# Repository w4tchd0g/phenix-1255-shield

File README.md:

# phenix-1255-shield

Expansion board (shield) for the NXP **FRDM-MCXN947** development board, built around the Semtech **SX1255** RF transceiver (TX 440 MHz, RX 430 MHz).

Together with the firmware it turns the FRDM board into a multimode SDR transceiver for base stations: TETRA today, DMR, FM and more modes planned. The I/Q samples are streamed to a host over HS USB or Ethernet.

This board is the hardware part of [phenix-1255-sw](https://github.com/w4tchd0g/phenix-1255-sw). It is a modified version of [Phenix-1255-HW](https://github.com/labdvm/Phenix-1255-HW) by Z32IT ([@labdvm](https://github.com/labdvm)), see [Changes from Phenix-1255-HW](#changes-from-phenix-1255-hw).

> **Status:** design complete and ready for fabrication. The schematic passes ERC without errors, the PCB passes DRC without errors and without unrouted connections. The Gerber files for JLCPCB and PCBWay are in [`production/`](#fabrication). Before the first power-up, read the [bring-up checklist](#bring-up-checklist).

## Preview

| Top | Bottom |
|---|---|
|  |  |

### SMA connector options

J5 (TX) and J6 (RX) use a hybrid land pattern that takes either connector type. Populate only one connector per port.

| Vertical SMD jack (CONSMA001-SMD-G) | Edge mount (Samtec SMA-J-P-H-ST-EM1) |
|---|---|
|  |  |

- **CONSMA001-SMD-G:** reflowed with the other parts. The unused edge-mount centre pad forms a short open stub (about 1 pF). At 430/440 MHz it has practically no effect (return loss at the port ≥ 34 dB).
- **Edge mount:** the edge-mount pads have no paste, so solder the jack by hand after reflow. The GND pads connect to the fill through thermal reliefs to make this easier. Use a large chisel tip and preheat the board from below (about 120–150 °C).

## Changes from Phenix-1255-HW

The basic hardware concept comes from [labdvm/Phenix-1255-HW](https://github.com/labdvm/Phenix-1255-HW) (Copyright © Z32IT 2026, CERN-OHL-P-2.0). This project changes revision V2 of it as follows (2026-11):

**RF**

- **Antenna matching:** new matching networks. TX: an L-network transforms the 50 Ω of the LFCN-490+ to the 100 Ω optimum load of RFO_P (before: 100 pF straight to the filter). RX: 100 pF / 33 nH / 68 nH for the 200 Ω LNA input (before: 39 nH series, 82 nH shunt). See [RF matching networks](#rf-matching-networks).
- **RF connectors:** SMA instead of U.FL, with a hybrid land pattern for J5/J6 that takes either a vertical SMD jack or an edge-mount jack, see [SMA connector options](#sma-connector-options).
- **Port protection:** each SMA port has a 100 nH DC shunt and a low-capacitance TVS diode (before: 1 MΩ to GND). A BAV99 limiter protects the RX input of the SX1255.
- **PCB:** 4 layers instead of 2, with 50 Ω coplanar waveguides on a solid GND plane, via fences along the RF lines and a GND stitching grid, see [PCB](#pcb). No mounting holes.
- **Reference clock:** 2520 footprint only, TCXO AC-coupled to XTB through 10 nF (before: direct connection with 10 kΩ / 10 pF to GND).

**Power**

- **3.3 V regulator:** an ST LDK130M33R (SOT-23-5) replaces the Microchip MCP1703A (SOT-223). It runs directly from `+5v0`; the PTC fuse, the TVS array and the ferrite bead at the input are gone.
- **Supply split:** the LDO only supplies the RF part (SX1255, TCXO, PA load switch). Display, buttons and jumpers run from the FRDM 3.3 V rail. The 1 Ω series resistors in the SX1255 supply pins are gone. See [Power](#power).
- **PA supply switching:** an integrated load switch (TPS22917) replaces the P-channel MOSFET. The *bypass* solder jumper is gone.

**Digital interface and MCU pins**

- **`~PA_EN` pin:** moved from P2_4 to P1_23 (J9.23) for better routing.
- **Series resistors:** 33 Ω at the driving end of each SX1255 signal. NSS has a 10 kΩ pull-up, CK_IN and Q_IN are bridged and pulled down with one 10 kΩ resistor, `SX_RST` has no series resistor.
- **Hardware ID:** three solder jumpers (JP1–JP3, `HW_ID_0`…`HW_ID_2`) encode the board version, so that the firmware can support several hardware versions (up to 8). This board is **hardware ID 0** (all jumpers open).
- **Buttons:** Panasonic EVQ-Q2 instead of C&K PTS647. *OK* and *→* swapped pins: *OK* is now on P1_22 (J3.3), *→* on P4_12 (J4.1).
- **Status LEDs:** five instead of four; the new PA LED lights while the PA is powered. The LEDs on the GPIOs were reassigned: P0_14 green *OK* (before: red *Err*), P0_22 yellow *INFO* (before: *Warn*), P0_15 red *ERR* (before: green *Good*). 1 kΩ instead of 1.5 kΩ series resistors.
- **Display:** footprint with the module outline (DS1) instead of a 1×4 socket, without series resistors in SCL/SDA.

See [MCU pin assignment](#mcu-pin-assignment) for the pins. The TX driver amplifier of the *V2 Plus* variant is not part of this design.

## Overview

| | |
|---|---|
| Base board | [NXP FRDM-MCXN947](https://www.nxp.com/design/design-center/development-boards-and-designs/FRDM-MCXN947) |
| EDA tool | KiCad 10 |
| Board size | 118 × 55 mm, R2 corners, 17 × 5 mm cutout (R1 corners) on the left edge for the Ethernet jack of the FRDM board |
| Stackup | 4 layers, 1.6 mm, JLCPCB JLC04161H-7628 |
| Assembly | all parts on the top side |
| Based on | [Phenix-1255-HW](https://github.com/labdvm/Phenix-1255-HW) by Z32IT (CERN-OHL-P-2.0), see [Changes from Phenix-1255-HW](#changes-from-phenix-1255-hw) |
| Shield template | FRDM-MCXN947 shield template from [wavenumber-eng/frdm-templates](https://github.com/wavenumber-eng/frdm-templates) (CC0): board outline, header placement and root schematic |

## Components

| Function | Part | Manufacturer |
|---|---|---|
| RF transceiver | SX1255IWLTRT (QFN-32, 5 × 5 mm) | Semtech |
| Reference clock | TG2520SMN 38.4 MHz TCXO (2.5 × 2.0 mm) | Epson |
| SAW filter 430 MHz (RX) | TA0655A | Tai-Saw |
| Low-pass filter (TX) | LFCN-490+ | Mini-Circuits |
| RF connectors (TX, RX) | CONSMA001-SMD-G (vertical, SMD) or SMA-J-P-H-ST-EM1 (edge mount), see [SMA connector options](#sma-connector-options) | TE / Linx, Samtec |
| ESD protection RF ports | PESD5V0F1BL | Nexperia |
| RX input limiter | BAV99 | Nexperia |
| LDO 3.3 V | LDK130M33R | ST |
| PA supply load switch | TPS22917LDBVR (active-low enable) | TI |
| Display | OLED 0.96″ 128×64, SSD1306, I²C, pin order GND/VDD/SCL/SDA (module with on-board pull-ups) | – |
| Tactile switch (SPST-NO, 6.5 × 6 mm, SMD), 3× | EVQ-Q2Y03W | Panasonic |
| Status LEDs 0603, 5× (PWR, PA, OK, INFO, ERR) | 150060xS75000 (green, yellow, red) | Würth |
| Hardware ID, 3× | solder jumper, open (hardware ID 0) | – |
| Headers to the FRDM board | Samtec SSQ (from the template) | Samtec |

Passives are 0603 (resistors UNI-ROYAL `0603WAF…`, capacitors Samsung/Murata/Yageo, RF inductors Murata `LQW18AN…`). The manufacturer part numbers are stored in the `MPN` field of the symbols.

## Circuit

### Power

| Net | Source | Loads |
|---|---|---|
| `+5v0` | FRDM header J3.10 | LDO input |
| `+3.3V_LDO` | LDO on the shield (enable tied to `+5v0`) | SX1255 VBAT1/VBAT2, TCXO, load switch input, PWR LED |
| `VBAT3` | load switch, controlled by `~PA_EN` | SX1255 VBAT3 (PA supply), PA LED |
| `+3v3` | FRDM header (J3.4, J3.8, J9.21, J8.1) | display, buttons, HW-ID jumpers, `~PA_EN` pull-up |

The RF part runs from its own low-noise LDO. Only the MCU-side parts use the FRDM 3.3 V rail.

`~PA_EN` is **active low** and pulled up to `+3v3` with 100 kΩ, so the PA supply stays off until the firmware drives the pin low. The load switch uses quick output discharge (QOD tied to VOUT). CT is left open, which gives the fastest turn-on.

### RF

- **TX:** SX1255 RFO_P → matching network (100 pF / 3.6 pF / 18 nH) → LFCN-490+ low-pass → SMA **J5 (TX)**. RFO_N is AC-coupled to GND.
- **RX:** SMA **J6 (RX)** → TA0655A SAW filter → matching network (100 pF / 33 nH / 68 nH) → SX1255 RFI, with a BAV99 limiter at the RFI pin.
- **SMA ports:** each port has a 100 nH DC shunt to GND (L1/L5) and a low-capacitance TVS diode (D1/D8). Together with the stub of the SMD jack they need no further matching (return loss ≥ 24 dB).
- **RF lines:** 50 Ω coplanar waveguide with ground (CPWG) on F.Cu over the solid GND plane In1, 0.30 mm track, 0.30 mm gap (0.20 mm inside the SX1255 courtyard). A field-solver check gives about 52 Ω with solder mask, i.e. a return loss of about 33 dB. The lines are electrically short (longest RF net 23 mm ≈ 23° at 440 MHz).
- **Reference clock:** the 38.4 MHz TCXO drives XTB through 10 nF, XTA is left open (TCXO connection per the datasheet). 38.4 MHz is above the specified FXOSC range of the SX1255 (32 / 36 / 36.864 MHz min/typ/max, datasheet Rev. 3.0, table 5). It has been **tested and works**; keep in mind that it is outside the specification. All frequencies derived from FXOSC (PLL step, I/Q sample rate) scale with 38.4 MHz.

`scripts/rf_calc.py` reproduces all RF numbers in this README (CPWG impedance, SMA stub, port shunts, matching networks). It runs with the standard library; the field solver part also needs numpy and scipy (`pip install numpy scipy`).

### RF matching networks

The networks adapt the SX1255 impedances to the 50 Ω of the LFCN-490+ and the TA0655A. They are based on the SX1255 datasheet (Rev. 3.0) and on separate front-end design notes (*SX1255 RF front end: TX 440 MHz / RX 430 MHz*, not in this repository). The values are calculated with ideal components and are **start values**; the final tuning is done on the board with a VNA.

#### TX: 100 Ω → 50 Ω

```
RF_OP ──C14 100p──┬──L2 18n──► LFCN-490+ (50 Ω) ──► J5
                  │
               C13 3.6p
                  │
                 GND
RF_ON ──C15 100p── GND
```

The datasheet specifies an optimum load of **100 Ω differential** between RF_OP and RF_ON (section 3.4.4, peak output power +5 dBm). The output is used single-ended: C15 ties RF_ON to ground for RF, so RF_OP has to see 100 Ω. The low-pass L-network (Q = 1) transforms 50 Ω up to 100 Ω:

| Element | Calculated | Used |
|---|---|---|
| Shunt C | 3.62 pF | **C13 = 3.6 pF** (C0G, ±0.1 pF) |
| Series L | 18.09 nH | **L2 = 18 nH** (wirewound, ±2 %) |

C14 (100 pF) only blocks DC. With the values used, RF_OP sees 99.5 − j3.1 Ω at 440 MHz (return loss 35.9 dB, ≥ 22 dB from 400 to 480 MHz, ≥ 29.9 dB within the component tolerances). The network adds 3.3 dB attenuation at the 2nd and 9.5 dB at the 3rd harmonic on top of the LFCN-490+.

**Tuning element: C13.** The output capacitance of RF_OP is not specified and appears in parallel with C13. Trim C13 for maximum output power at J5.

#### RX: 50 Ω → 200 Ω

```
J6 ──► TA0655A (50 Ω) ──C21 100p──L4 33n──┬────────┬────────┬──► RF_IN (200 Ω)
                                          │        │        │
                                        L3 68n   D4 BAV99  C_pin (LNA input)
                                          │        │        │
                                         GND      GND      GND
```

RF_IN is a common-gate LNA with an input impedance of 50 Ω or 200 Ω, selected with the bit LnaZin in RegRxAnaGain (section 3.6.2). The network is designed for **200 Ω** (see [Firmware notes](#firmware-notes)).

The ideal L-network at 430 MHz is a series L of 32.05 nH (**L4 = 33 nH**) and a shunt C of 3.21 pF at RF_IN. There is no shunt capacitor on the board: that capacitance comes from the RF_IN node itself (LNA input, BAV99, pad, track). The design assumes it is larger than needed, and **L3 (68 nH)** compensates the excess (68 nH cancels 2.01 pF at 430 MHz). L3 also gives RF_IN a DC path to ground. The values used require a **total capacitance of 5.24 pF at RF_IN**. The datasheet does not specify it, so this is the critical assumption of the RX match:

| Total capacitance at RF_IN | Return loss at 430 MHz | Best match at |
|---|---|---|
| 4.0 pF | 10.0 dB | 495 MHz |
| 4.5 pF | 14.2 dB | 466 MHz |
| 5.0 pF | 23.7 dB | 441 MHz |
| **5.24 pF** | **40.0 dB** | **431 MHz** |
| 5.5 pF | 23.1 dB | 420 MHz |
| 6.0 pF | 14.0 dB | 401 MHz |

With the nominal value the return loss is ≥ 20 dB from 414 to 447 MHz, much wider than the 4 MHz passband of the TA0655A.

**Tuning element: L3.** For a match at 430 MHz: 4 pF → 177 nH, 5 pF → 77 nH, 6 pF → 49 nH, 7 pF → 36 nH. Procedure (from the design notes): before the TA0655A is fitted, solder a coax pigtail to its output pad (pin E) and measure S11 towards the SX1255. If the minimum is above 430 MHz, increase L3; if it is below, decrease L3. Adjust the depth with L4 (27 / 33 / 39 nH). Target S11 ≤ −10 dB, then optimise for best sensitivity.

### Digital interface

All signals between the SX1255 and the headers have 33 Ω series resistors at the driving end: next to the SX1255 for its outputs (`CK_OUT`, `I_OUT`, `MISO`, `DIO0..3`), next to the headers for the MCU outputs (`SCK`, `MOSI`, `NSS`, `I_IN`). NSS has a 10 kΩ pull-up to `+3.3V_LDO`. CK_IN and Q_IN are unused inputs: pins 11 and 12 are bridged next to the SX1255 and pulled down together with one 10 kΩ resistor (R4). Q_OUT and XTA are not connected.

## MCU pin assignment

| Net | Header | FRDM signal | Function |
|---|---|---|---|
| `SCK` | J2.12 | P0_25 / FC1_SCK | SX1255 SPI |
| `MISO` | J2.10 | P0_26 / FC1_SDI | SX1255 SPI |
| `MOSI` | J2.8 | P0_24 / FC1_SDO | SX1255 SPI |
| `NSS` | J1.16 | P0_31 | SX1255 SPI chip select (GPIO) |
| `SX_RST` | J1.6 | P0_29 | SX1255 reset (active high) |
| `DIO0` | J2.2 | P0_28 | SX1255 DIO0 |
| `DIO1` | J1.10 | P0_30 / P4_13 | SX1255 DIO1 |
| `DIO2/WS` | J1.13 | P3_19 / SAI1_RX_FS | SX1255 DIO2, I/Q word select |
| `DIO3` | J2.13 | P0_19 | SX1255 DIO3 |
| `CK_OUT` | J1.9 | P3_18 / SAI1_RX_BCLK | I/Q bit clock from SX1255 |
| `I_OUT` | J1.15 | P3_21 / SAI1_RXD0 | I/Q data SX1255 → MCU |
| `I_IN` | J1.5 | P3_20 / SAI1_TXD0 | I/Q data MCU → SX1255 |
| `~PA_EN` | J9.23 | P1_23 / EZH_LCD_RD | PA supply enable, active low |
| `SDA` | J2.17 | P1_0 | Display I²C |
| `SCL` | J2.15 | P1_1 | Display I²C |
| `BTN_0` | J3.1 | P2_0 | Button S1 (`<--`) |
| `BTN_1` | J3.3 | P1_22 | Button S2 (`OK`) |
| `BTN_2` | J4.1 | P4_12 / P0_21 | Button S3 (`-->`) |
| `LED_0` | J4.6 | P0_14 | LED OK (green) |
| `LED_1` | J4.8 | P0_22 | LED INFO (yellow) |
| `LED_2` | J4.10 | P0_15 (solder jumper SJ8 1-2, FRDM default) | LED ERR (red) |
| `HW_ID_0` | J9.5 | P1_19 / EZH_LCD_D15_CAMERA_RST | Hardware ID bit 0 |
| `HW_ID_1` | J9.12 | P3_4 | Hardware ID bit 1 |
| `HW_ID_2` | J9.11 | P3_5 | Hardware ID bit 2 |

Where the template lists two MCU pins (e.g. `P0_15 / P2_0`), the FRDM board routes the header pin to one of them via a solder jumper or resistor option. The pins above are the defaults from the FRDM-MCXN947 user manual (UM12018 Rev. 2.0). Some MCU pins also reach a second header on the FRDM board; on this shield the second pin is always left unconnected:

- P2_0 (`BTN_0`, J3.1) also goes to J9.25 (R167). It only reaches J4.10 if SJ8 is changed to 2-3, which would short `BTN_0` and `LED_2`. **Leave SJ8 on the FRDM board in its default position 1-2.**
- P1_22 (`BTN_1`, J3.3) also goes to J9.24.
- P1_23 (`~PA_EN`, J9.23) also goes to J1.8 (SJ1 1-2, default).

### Firmware notes

- **Buttons and HW-ID jumpers** switch to `+3v3` and have no external pull-downs. Enable the **internal pull-downs** on `BTN_x` and `HW_ID_x`. A pressed button or a closed jumper reads as `1`.
- **LEDs** `LED_0..2` are active high (1 kΩ to the LED). The PWR LED is always on, the PA LED lights while `VBAT3` is powered.
- **`SX_RST`** must stay **floating** in normal operation, as required by the SX1255 datasheet. Configure the GPIO as an input without pull resistor and drive it high only to reset.
- **`~PA_EN`**: drive it low to power the PA, drive it high or release it to switch the PA off.
- **LNA input impedance**: keep LnaZin (RegRxAnaGain, register 0x0C bit 0, reset value 1) at 1 = 200 Ω. The RX matching is designed for it; 50 Ω detunes the RX input.
- **I/Q interface**: SAI1 receives with the bit clock and frame sync from the SX1255; the transmitter has to run synchronously to the receiver.
- **Reference clock**: FXOSC is 38.4 MHz, not the 36 MHz of the datasheet examples. Calculate PLL and sample-rate settings with 38.4 MHz.

## PCB

### Stackup

JLCPCB JLC04161H-7628, 1.6 mm, 4 layers:

| Layer | Use | Dielectric to next layer |
|---|---|---|
| F.Cu | signals and RF (CPWG), GND fill | 0.21 mm prepreg 7628, εr 4.4 |
| In1.Cu | solid GND plane, no routing | 1.065 mm core, εr 4.6 |
| In2.Cu | power plane (`+3v3`, `+3.3V_LDO` and `+5v0` areas), GND below the RF section | 0.21 mm prepreg 7628, εr 4.4 |
| B.Cu | signals (SPI, DIO, SDA), GND fill | – |

The RF section has no vias in the signal path and no tracks on the inner layers or B.Cu. The GND layers are tied together with via fences along the RF lines and a stitching grid; the SX1255 exposed pad has thermal vias. Design minimums: 0.15 mm track and clearance, 0.3 mm drill, 0.5 mm via diameter (vias used: 0.6 / 0.3 mm and 0.8 / 0.4 mm).

## Fabrication

Production files are in `production/`:

- `production/phenix-1255-shield-gerber.zip` – upload this to JLCPCB or PCBWay (Gerber X1, Protel extensions, Excellon drill, PTH and NPTH separate).
- `production/gerber/` – the same files unpacked, plus the drill maps.

Order settings:

- **JLCPCB:** 4 layers, 1.6 mm, stackup **JLC04161H-7628** (the RF lines are calculated for it), 1 oz outer copper.
- **PCBWay:** 4 layers, 1.6 mm, 1 oz outer copper. The standard stackup is not guaranteed to match, so specify the [stackup](#stackup) in the order remark: layer order F.Cu (`.gtl`), In1.Cu (`.g1`), In2.Cu (`.g2`), B.Cu (`.gbl`); 0.21 mm prepreg 7628 between F.Cu and In1.Cu. The 50 Ω CPWG on F.Cu (0.30 mm track, 0.30 mm gap to the coplanar GND, reference In1.Cu) depends on that prepreg thickness.

Regenerate the files after every layout change:

```sh
./scripts/gerber.sh   # aborts if the DRC reports errors or unconnected items
./scripts/render.sh   # updates the images in docs/img/
```

### Assembly notes

- All SMD parts are on the top side. Populate **one** SMA connector type per port (see [SMA connector options](#sma-connector-options)).
- The FRDM headers J1–J4, J8 and J9 are marked *Do not populate* on the PCB, so they are not in a BOM or position file exported from the PCB. Solder them by hand.
- This board is **hardware ID 0**: leave the jumpers JP1–JP3 open. Do not bridge them, otherwise the firmware detects a different hardware version.
- If the RX match is to be measured (see [RF matching networks](#rf-matching-networks)), leave the TA0655A off the first board.

## Bring-up checklist

These points cannot be checked on paper and need a measurement on the first board:

- **TX output:** check the single-ended output on RFO_P (no DC feed) against the Semtech reference design, and trim C13 for maximum output power.
- **RX match:** the match assumes 5.24 pF at RF_IN, which the datasheet does not specify. Measure S11 at the TA0655A output and adjust L3/L4.
- **PA supply:** confirm that the SX1255 tolerates VBAT3 switched off while VBAT1/VBAT2 are powered.
- **Reference clock:** 38.4 MHz is outside the SX1255 specification (tested and working, see [RF](#rf)).

## Project structure

```
phenix-1255-shield/
├── phenix-1255-shield.kicad_pro    # project file – open this one
├── phenix-1255-shield.kicad_sch    # root schematic: FRDM headers, PWR_FLAGs
├── schematic.kicad_sch             # sub-sheet: SX1255, RF, power, UI
├── phenix-1255-shield.kicad_pcb    # PCB
├── phenix-1255-shield.kicad_dru    # custom design rules (RF, stitching)
├── phenix-1255-shield.kicad_sym    # symbols from the template
├── sym-lib-table / fp-lib-table    # project libraries
├── empty.kicad_wks                 # drawing sheet
├── scripts/gerber.sh               # Gerber and drill files for JLCPCB and PCBWay
├── scripts/render.sh               # renders the images in docs/img/
├── scripts/sma_variant.py          # helper for render.sh: SMD / edge-mount SMA view
├── scripts/trim.py                 # helper for render.sh: crops the images to the board
├── scripts/rf_calc.py              # CPWG impedance, SMA stub and matching network calculation
├── scripts/make_3d_models.py       # generates the simplified 3D models in ext_parts/3d/
├── docs/img/                       # rendered PCB images
├── production/                     # Gerber and drill files (generated)
├── ext_parts/                      # project-specific symbols, footprints and 3D models
└── LICENSE                         # CERN-OHL-P-2.0
```

## Usage

1. Clone the repository.
2. Open `phenix-1255-shield.kicad_pro` in KiCad 10.

The project-specific libraries are linked relative to the project via `${KIPRJMOD}`. Standard parts and their 3D models come from the KiCad 10 libraries that are installed with KiCad. Nothing else needs to be installed or configured.

**Notes:**

- According to NXP, the connectors in the template are 2–6 mil off from the exact Arduino positions. This is a design bug of the FRDM-MCXN947 itself; the shield still mates with the board.
- Always double-check the header IO assignments against the current FRDM-MCXN947 documentation before ordering boards.

## License

This project (schematics, PCB, the libraries in `ext_parts/`, scripts and documentation) is a modified version of [Phenix-1255-HW](https://github.com/labdvm/Phenix-1255-HW), Copyright © Z32IT 2026 (see [Changes from Phenix-1255-HW](#changes-from-phenix-1255-hw)), and is licensed under the [CERN Open Hardware Licence Version 2 – Permissive](LICENSE) (CERN-OHL-P-2.0), except for the third-party content listed below.

Third-party content:

- **Shield template** ([wavenumber-eng/frdm-templates](https://github.com/wavenumber-eng/frdm-templates), FRDM-MCXN947 KiCad template): board outline, header footprints and their placement, root schematic with the header symbols (`phenix-1255-shield.kicad_sch`, `phenix-1255-shield.kicad_sym`). [CC0 1.0](https://creativecommons.org/publicdomain/zero/1.0/)
- **Display footprint** `Display_128x64_096_I2C`: by TG9541 ([kicad-footprints](https://github.com/TG9541/kicad-footprints)), [CC0 1.0](https://creativecommons.org/publicdomain/zero/1.0/)
- **SMA edge-mount option:** the edge-mount pads in `CONSMA001-SMD-G_EdgeHybrid` and the 3D model `SMA_Samtec_SMA-J-P-H-ST-EM1_EdgeMount.step` are derived from the [KiCad libraries](https://www.kicad.org/libraries/license/) (footprint and 3D model `SMA_Samtec_SMA-J-P-H-ST-EM1_EdgeMount`), [CC-BY-SA 4.0](https://creativecommons.org/licenses/by-sa/4.0/). The changes (merged land pattern, added insulator and centre socket) are under the same license.
- **Standard parts:** footprints and 3D models from the KiCad libraries are referenced, not included (CC-BY-SA 4.0 with the KiCad library exception for designs).

Datasheets are not part of this repository; the `Datasheet` field of each part links to the manufacturer.

This source is distributed **WITHOUT ANY EXPRESS OR IMPLIED WARRANTY, INCLUDING OF MERCHANTABILITY, SATISFACTORY QUALITY AND FITNESS FOR A PARTICULAR PURPOSE**. Please see the CERN-OHL-P-2.0 for applicable conditions.

Source location: <https://github.com/w4tchd0g/phenix-1255-shield>

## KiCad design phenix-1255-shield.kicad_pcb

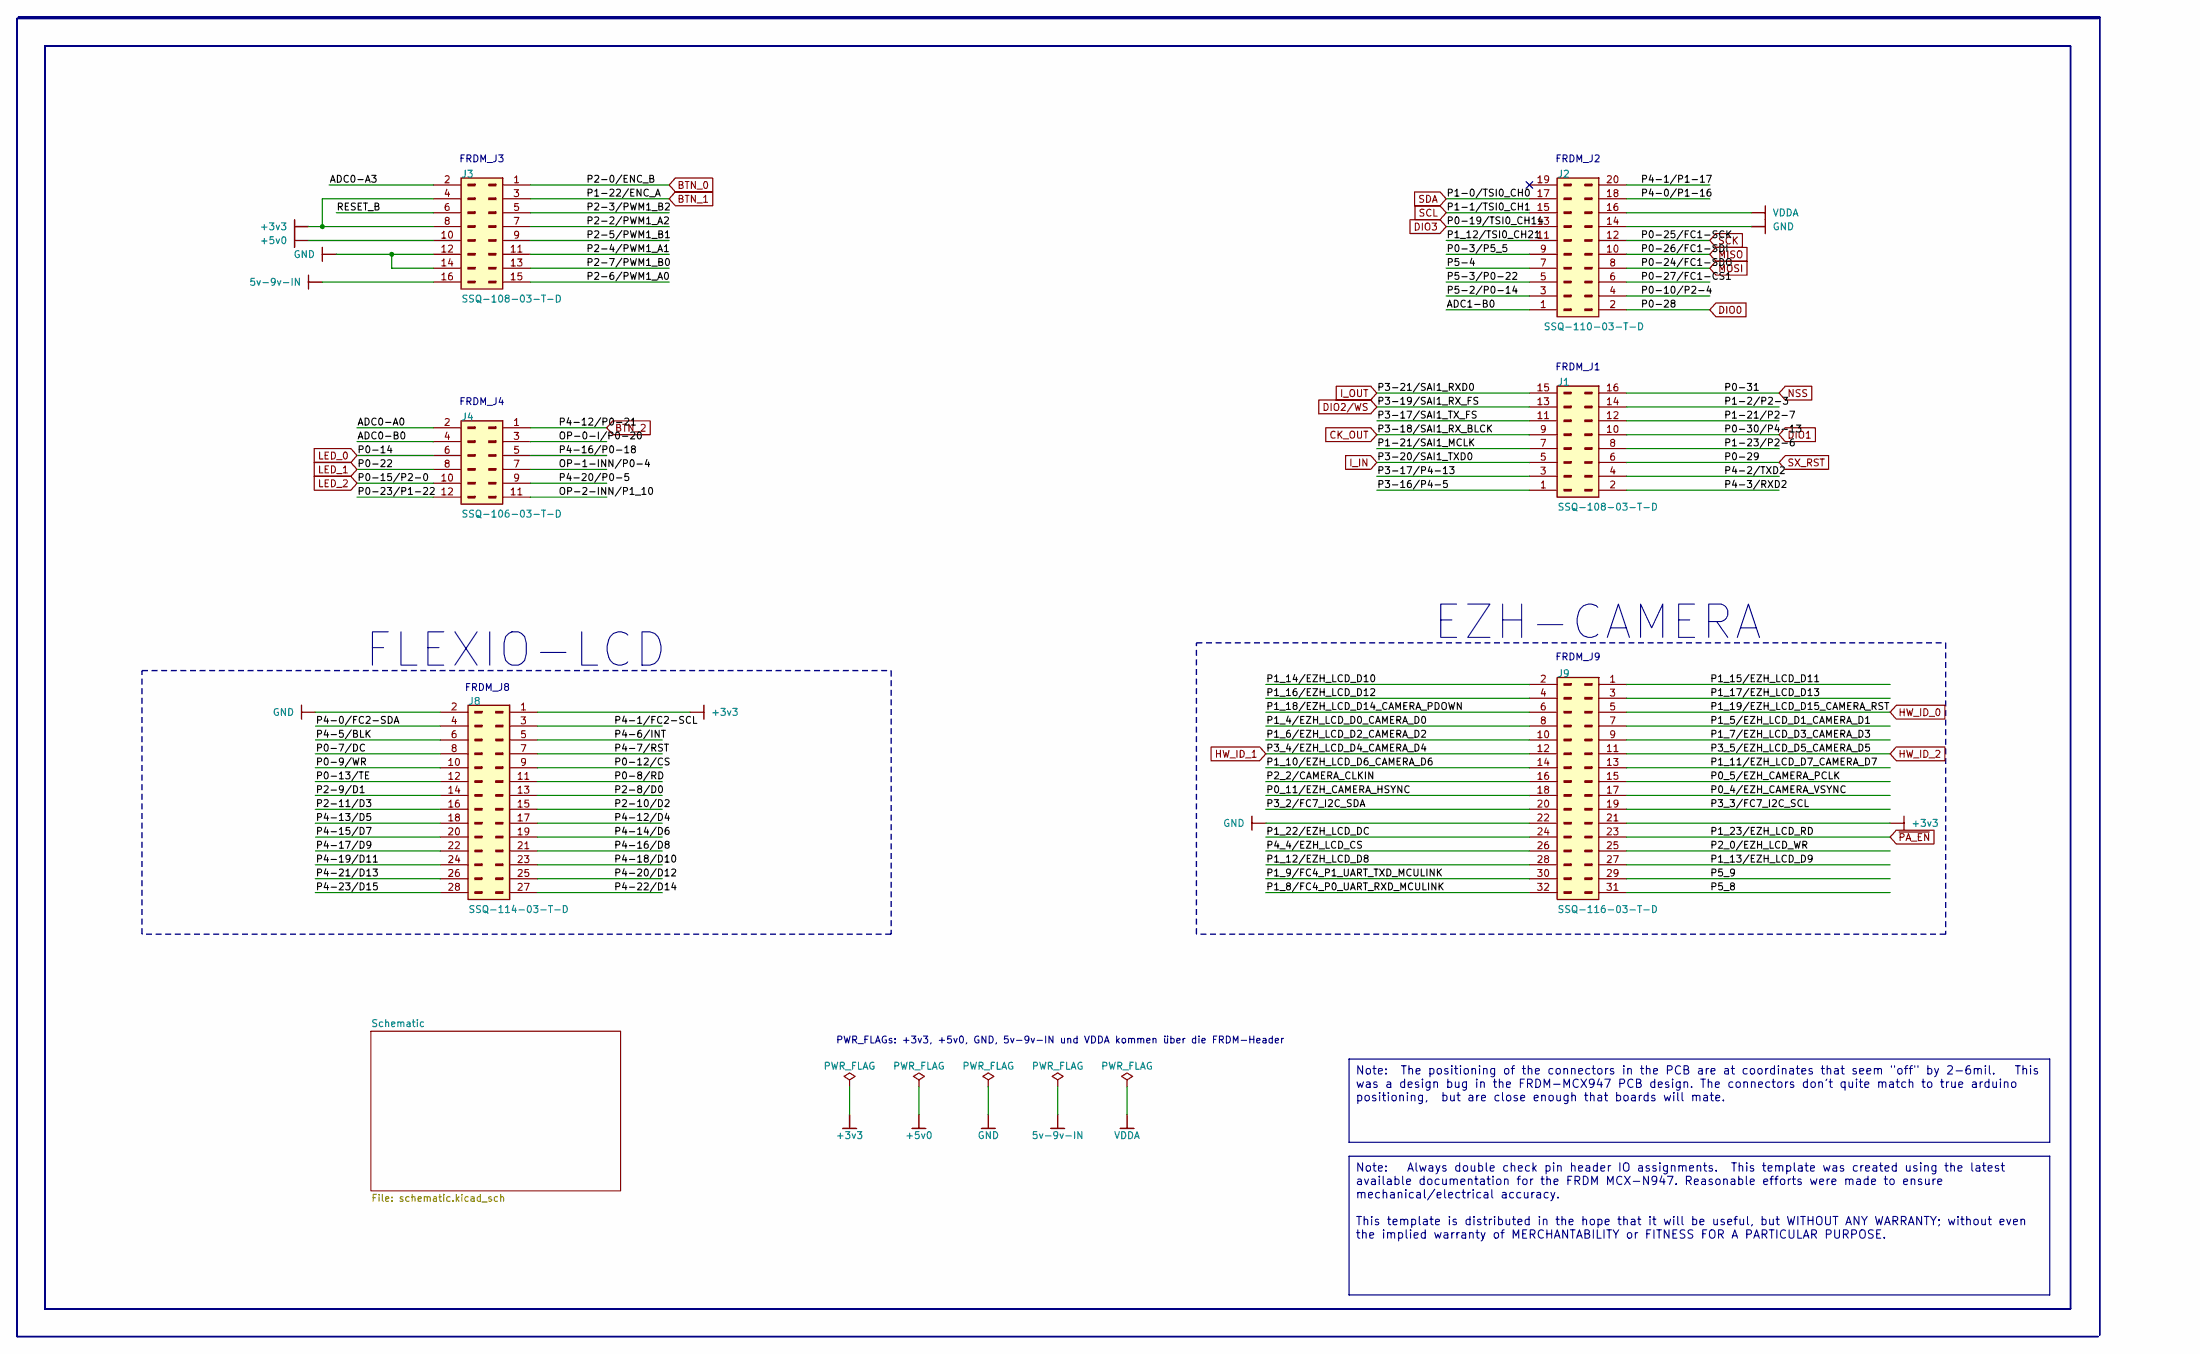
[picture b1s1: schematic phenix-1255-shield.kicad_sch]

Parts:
J1, J3: SSQ-108-03-T-D; MANUFACTURER PART NUMBER SSQ-108-03-T-D
J2: SSQ-110-03-T-D; MANUFACTURER PART NUMBER SSQ-110-23-T-D
J4: SSQ-106-03-T-D; MANUFACTURER PART NUMBER SSQ-106-03-T-D
J8: SSQ-114-03-T-D; MANUFACTURER PART NUMBER SSQ-114-03-T-D
J9: SSQ-116-03-T-D; MANUFACTURER P/N SSQ-116-03-T-D

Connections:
5v-9v-IN: J3.16
+3v3: J3.4, J3.8, J8.1, J9.21; also elsewhere on the board
+5v0: J3.10; also elsewhere on the board
/ADC0-A0: J4.2
/ADC0-A3: J3.2
/ADC0-B0: J4.4
/ADC1-B0: J2.1
/OP-0-I/P0-20: J4.3
/OP-1-INN/P0-4: J4.7
/OP-2-INN/P1_10: J4.11
/P0-3/P5_5: J2.9
/P0-7/DC: J8.8
/P0-8/RD: J8.11
/P0-9/WR: J8.10
/P0-10/P2-4: J2.4
/P0-12/CS: J8.9
/P0-13/TE: J8.12
/P0-23/P1-22: J4.12
/P0-27/FC1-CS1: J2.6
/P0_4/EZH_CAMERA_VSYNC: J9.17
/P0_5/EZH_CAMERA_PCLK: J9.15
/P0_11/EZH_CAMERA_HSYNC: J9.18
/P1-2/P2-3: J1.14
/P1-21/P2-7: J1.12
/P1-21/SAI1_MCLK: J1.7
/P1-23/P2-6: J1.8
/P1_4/EZH_LCD_D0_CAMERA_D0: J9.8
/P1_5/EZH_LCD_D1_CAMERA_D1: J9.7
/P1_6/EZH_LCD_D2_CAMERA_D2: J9.10
/P1_7/EZH_LCD_D3_CAMERA_D3: J9.9
/P1_8/FC4_P0_UART_RXD_MCULINK: J9.32
/P1_9/FC4_P1_UART_TXD_MCULINK: J9.30
/P1_10/EZH_LCD_D6_CAMERA_D6: J9.14
/P1_11/EZH_LCD_D7_CAMERA_D7: J9.13
/P1_12/EZH_LCD_D8: J9.28
/P1_12/TSI0_CH21: J2.11
/P1_13/EZH_LCD_D9: J9.27
/P1_14/EZH_LCD_D10: J9.2
/P1_15/EZH_LCD_D11: J9.1
/P1_16/EZH_LCD_D12: J9.4
/P1_17/EZH_LCD_D13: J9.3
/P1_18/EZH_LCD_D14_CAMERA_PDOWN: J9.6
/P1_22/EZH_LCD_DC: J9.24
/P2-2/PWM1_A2: J3.7
/P2-3/PWM1_B2: J3.5
/P2-4/PWM1_A1: J3.11
/P2-5/PWM1_B1: J3.9
/P2-6/PWM1_A0: J3.15
/P2-7/PWM1_B0: J3.13
/P2-8/D0: J8.13
/P2-9/D1: J8.14
/P2-10/D2: J8.15
/P2-11/D3: J8.16
/P2_0/EZH_LCD_WR: J9.25
/P2_2/CAMERA_CLKIN: J9.16
/P3-16/P4-5: J1.1
/P3-17/P4-13: J1.3
/P3-17/SAI1_TX_FS: J1.11
/P3_2/FC7_I2C_SDA: J9.20
/P3_3/FC7_I2C_SCL: J9.19
/P4-0/FC2-SDA: J8.4
/P4-0/P1-16: J2.18
/P4-1/FC2-SCL: J8.3
/P4-1/P1-17: J2.20
/P4-2/TXD2: J1.4
/P4-3/RXD2: J1.2
/P4-5/BLK: J8.6
/P4-6/INT: J8.5
/P4-7/RST: J8.7
/P4-12/D4: J8.17
/P4-13/D5: J8.18
/P4-14/D6: J8.19
/P4-15/D7: J8.20
/P4-16/D8: J8.21
/P4-16/P0-18: J4.5
/P4-17/D9: J8.22
/P4-18/D10: J8.23
/P4-19/D11: J8.24
/P4-20/D12: J8.25
/P4-20/P0-5: J4.9
/P4-21/D13: J8.26
/P4-22/D14: J8.27
/P4-23/D15: J8.28
/P4_4/EZH_LCD_CS: J9.26
/P5-2/P0-14: J2.3
/P5-3/P0-22: J2.5
/P5-4: J2.7
/P5_8: J9.31
/P5_9: J9.29
/RESET_B: J3.6
BTN_0: J3.1; also elsewhere on the board
BTN_1: J3.3; also elsewhere on the board
BTN_2: J4.1; also elsewhere on the board
CK_OUT: J1.9; also elsewhere on the board
DIO0: J2.2; also elsewhere on the board
DIO1: J1.10; also elsewhere on the board
DIO2/WS: J1.13; also elsewhere on the board
DIO3: J2.13; also elsewhere on the board
GND: J2.14, J3.12, J3.14, J8.2, J9.22; also elsewhere on the board
HW_ID_0: J9.5; also elsewhere on the board
HW_ID_1: J9.12; also elsewhere on the board
HW_ID_2: J9.11; also elsewhere on the board
I_IN: J1.5; also elsewhere on the board
I_OUT: J1.15; also elsewhere on the board
LED_0: J4.6; also elsewhere on the board
LED_1: J4.8; also elsewhere on the board
LED_2: J4.10; also elsewhere on the board
MISO: J2.10; also elsewhere on the board
MOSI: J2.8; also elsewhere on the board
NSS: J1.16; also elsewhere on the board
SCK: J2.12; also elsewhere on the board
SCL: J2.15; also elsewhere on the board
SDA: J2.17; also elsewhere on the board
SX_RST: J1.6; also elsewhere on the board
VDDA: J2.16
~PA_EN: J9.23; also elsewhere on the board

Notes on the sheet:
FRDM_J2
FRDM_J8
PWR_FLAGs: +3v3, +5v0, GND, 5v-9v-IN und VDDA kommen über die FRDM-Header
FRDM_J9
FRDM_J4
FRDM_J1
FLEXIO-LCD
FRDM_J3
EZH-CAMERA
Note: Always double check pin header IO assignments. This template was created using the latest available documentation for the FRDM MCX-N947. Reasonable efforts were made to ensure mechanical/electrical accuracy. This template is distributed in the hope that it will be useful, but WITHOUT ANY WARR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
Note: The positioning of the connectors in the PCB are at coordinates that seem "off" by 2-6mil. This was a design bug in the FRDM-MCX947 PCB design. The connectors don't quite match to true arduino positioning, but are close enough that boards will mate.

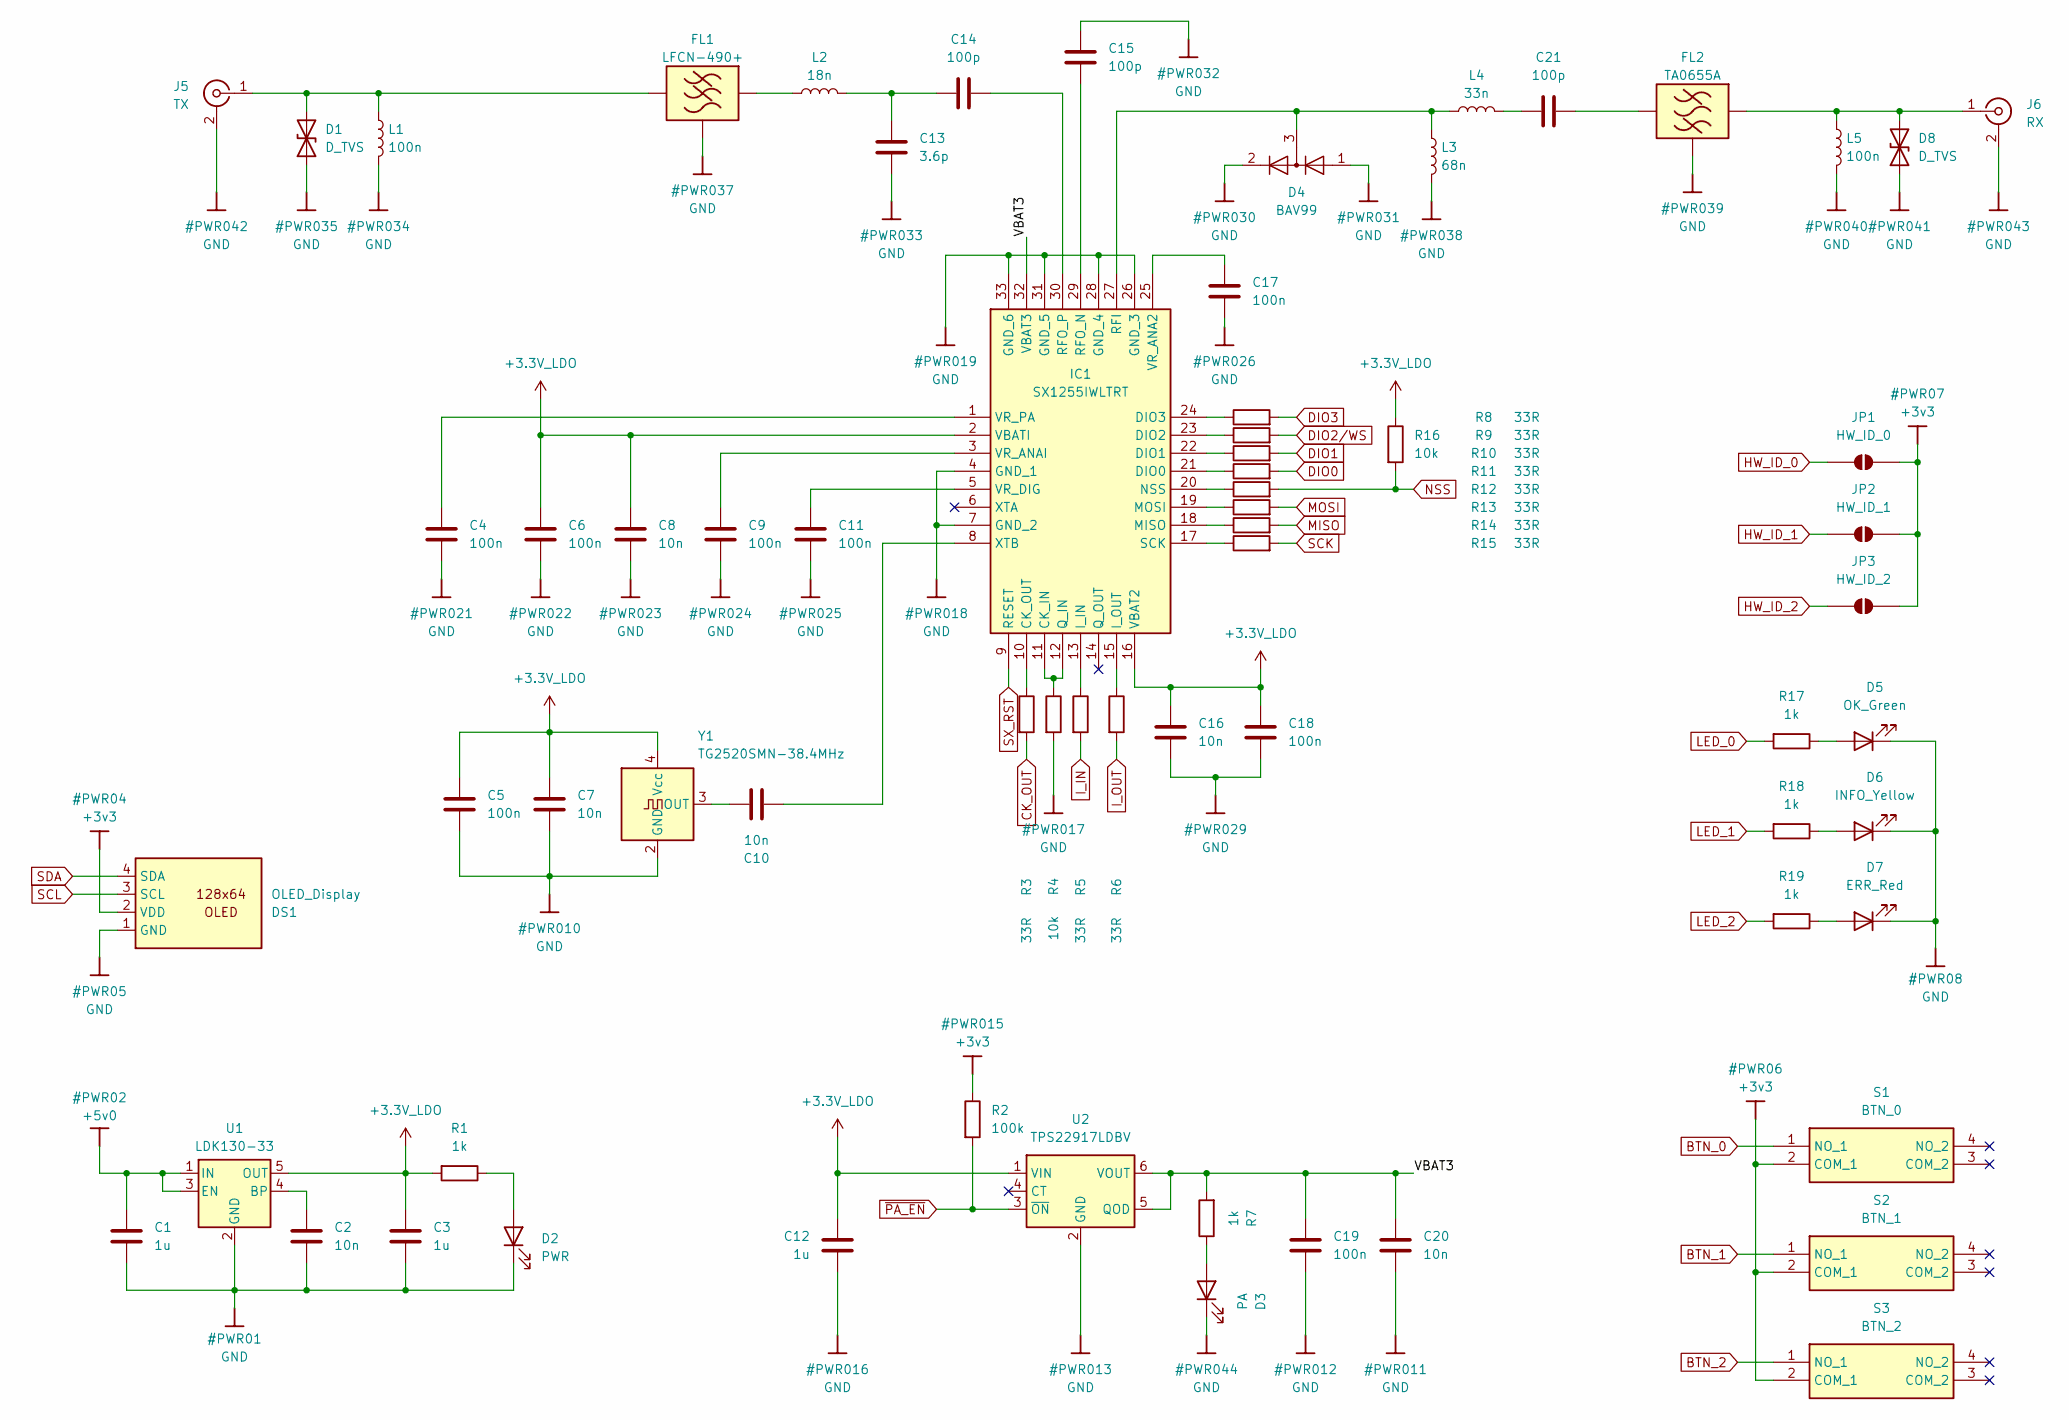
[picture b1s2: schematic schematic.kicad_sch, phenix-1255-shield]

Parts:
C1, C3, C12: 1u; C_0603_1608Metric; MPN CL10A105KL8NNNC; LCSC C478859
C2, C7, C8, C10, C16, C20: 10n; C_0603_1608Metric; MPN GRM1885C1H103JA01J; LCSC C2215227
C4, C5, C6, C9, C11, C17, C18, C19: 100n; C_0603_1608Metric; MPN CL10B104KB8NNNC; LCSC C1591
C13: 3.6p; C_0603_1608Metric; MPN CC0603BRNPO9BN3R6; LCSC C519106
C14, C15, C21: 100p; C_0603_1608Metric; MPN CL10C101JB8NNNC; LCSC C14858
D1, D8: D_TVS; D_SOD-882; MPN PESD5V0F1BL,315; LCSC C45961
D2: PWR; LED_0603_1608Metric; MPN 150060GS75000; LCSC 0
D3: PA; LED_0603_1608Metric; MPN 150060RS75000; LCSC 0
D4: BAV99; SOT-23; MPN BAV99,215; LCSC C2500
D5: OK_Green; LED_0603_1608Metric; MPN 150060GS75000; LCSC 0
D6: INFO_Yellow; LED_0603_1608Metric; MPN 150060YS75000; LCSC 0
D7: ERR_Red; LED_0603_1608Metric; MPN 150060RS75000; LCSC 0
DS1: OLED_Display; Display_128x64_096_I2C
FL1: LFCN-490+; LFCN490
FL2: TA0655A; MPN TA0655A
IC1: SX1255IWLTRT; QFN50P500X500X80-33N-D; MPN SX1255IWLTRT; LCSC C89372
J5: TX; CONSMA001-SMD-G_EdgeHybrid
J6: RX; CONSMA001-SMD-G_EdgeHybrid
JP1: HW_ID_0; SolderJumper-2_P1.3mm_Open_RoundedPad1.0x1.5mm
JP2: HW_ID_1; SolderJumper-2_P1.3mm_Open_RoundedPad1.0x1.5mm
JP3: HW_ID_2; SolderJumper-2_P1.3mm_Open_RoundedPad1.0x1.5mm
L1, L5: 100n; L_0603_1608Metric; MPN LQW18ANR10G00D; LCSC C98088
L2: 18n; L_0603_1608Metric; MPN LQW18AN18NG00D; LCSC C86133
L3: 68n; L_0603_1608Metric; MPN LQW18AN68NG00D; LCSC C86135
L4: 33n; L_0603_1608Metric; MPN LQW18AN33NJ10D; LCSC C701171
R1, R7, R17, R18, R19: 1k; R_0603_1608Metric; MPN 0603WAF1001T5E; LCSC C21190
R2: 100k; R_0603_1608Metric; MPN 0603WAF1003T5E; LCSC C25803
R3, R5, R6, R8, R9, R10, R11, R12, R13, R14, R15: 33R; R_0603_1608Metric; MPN 0603WAF330JT5E
R4, R16: 10k; R_0603_1608Metric; MPN 0603WAF1002T5E; LCSC C25804
S1: BTN_0; EVQQ2; MPN EVQQ2Y03W; LCSC C2828255
S2: BTN_1; EVQQ2; MPN EVQQ2Y03W; LCSC C2828255
S3: BTN_2; EVQQ2; MPN EVQQ2Y03W; LCSC C2828255
U1: LDK130-33; SOT-23-5; MPN LDK130M33R; LCSC C2969807
U2: TPS22917LDBV; SOT-23-6; MPN TPS22917LDBVR; LCSC C3235537
Y1: TG2520SMN-38.4MHz; Oscillator_SMD_SeikoEpson_TG2520SMN-xxx-xxxxxx-4Pin_2.5x2.0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; MPN TG2520SMN 38.4000M-MCGNNM3; LCSC C20341495

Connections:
+3.3V_LDO: C3.1, C5.1, C6.1, C7.1, C8.1, C12.1, C16.1, C18.1, IC1.2 (VBATI), IC1.16 (VBAT2), R1.2, R16.1, U1.5 (OUT), U2.1 (VIN), Y1.4 (Vcc)
+3v3: DS1.2 (VDD), JP1.2 (B), JP2.2 (B), JP3.2 (B), R2.1, S1.2 (COM_1), S2.2 (COM_1), S3.2 (COM_1); also elsewhere on the board
+5v0: C1.1, U1.1 (IN), U1.3 (EN); also elsewhere on the board
/Schematic/VBAT3: C19.1, C20.1, IC1.32 (VBAT3), R7.2, U2.5 (QOD), U2.6 (VOUT)
BTN_0: S1.1 (NO_1); also elsewhere on the board
BTN_1: S2.1 (NO_1); also elsewhere on the board
BTN_2: S3.1 (NO_1); also elsewhere on the board
CK_OUT: R3.2; also elsewhere on the board
DIO0: R11.2; also elsewhere on the board
DIO1: R10.2; also elsewhere on the board
DIO2/WS: R9.2; also elsewhere on the board
DIO3: R8.2; also elsewhere on the board
GND: C1.2, C2.2, C3.2, C4.2, C5.2, C6.2, C7.2, C8.2, C9.2, C11.2, C12.2, C13.2, C15.2, C16.2, C17.2, C18.2, C19.2, C20.2, D1.1 (A1), D2.1 (K), D3.1 (K), D4.1 (K), D4.2 (A), D5.1 (K), D6.1 (K), D7.1 (K), D8.1 (A1), DS1.1 (GND), FL1.2 (GROUND_1), FL1.4 (GROUND_2), FL2.1 (A_GND), FL2.3 (C_GND), FL2.4 (D_GND), FL2.6 (F_GND), IC1.4 (GND_1), IC1.7 (GND_2), IC1.26 (GND_3), IC1.28 (GND_4), IC1.31 (GND_5), IC1.33 (GND_6), J5.2 (Ext), J6.2 (Ext), L1.2, L3.2, L5.2, R4.2, U1.2 (GND), U2.2 (GND), Y1.2 (GND); also elsewhere on the board
HW_ID_0: JP1.1 (A); also elsewhere on the board
HW_ID_1: JP2.1 (A); also elsewhere on the board
HW_ID_2: JP3.1 (A); also elsewhere on the board
I_IN: R5.2; also elsewhere on the board
I_OUT: R6.2; also elsewhere on the board
LED_0: R17.2; also elsewhere on the board
LED_1: R18.2; also elsewhere on the board
LED_2: R19.2; also elsewhere on the board
MISO: R14.2; also elsewhere on the board
MOSI: R13.2; also elsewhere on the board
NSS: R12.2, R16.2; also elsewhere on the board
unnamed: C13.1, C14.1, L2.2
unnamed: C21.1, L4.2
unnamed: D1.2 (A2), FL1.3 (RF_OUT), J5.1 (In), L1.1
unnamed: D2.2 (A), R1.1
unnamed: D3.2 (A), R7.1
unnamed: D5.2 (A), R17.1
unnamed: D6.2 (A), R18.1
unnamed: D7.2 (A), R19.1
unnamed: D8.2 (A2), FL2.2 (B_IN), J6.1 (In), L5.1
unnamed: FL1.1 (RF_IN), L2.1
unnamed: C21.2, FL2.5 (E_OUT)
unnamed: IC1.11 (CK_IN), IC1.12 (Q_IN), R4.1
unnamed: IC1.10 (CK_OUT), R3.1
unnamed: IC1.21 (DIO0), R11.1
unnamed: IC1.22 (DIO1), R10.1
unnamed: IC1.23 (DIO2), R9.1
unnamed: IC1.24 (DIO3), R8.1
unnamed: IC1.13 (I_IN), R5.1
unnamed: IC1.15 (I_OUT), R6.1
unnamed: IC1.18 (MISO), R14.1
unnamed: IC1.19 (MOSI), R13.1
unnamed: IC1.20 (NSS), R12.1
unnamed: D4.3 (K), IC1.27 (RFI), L3.1, L4.1
unnamed: C15.1, IC1.29 (RFO_N)
unnamed: C14.2, IC1.30 (RFO_P)
unnamed: IC1.17 (SCK), R15.1
unnamed: C17.1, IC1.25 (VR_ANA2)
unnamed: C9.1, IC1.3 (VR_ANAI)
unnamed: C11.1, IC1.5 (VR_DIG)
unnamed: C4.1, IC1.1 (VR_PA)
unnamed: C10.2, IC1.8 (XTB)
unnamed: C2.1, U1.4 (BP)
unnamed: C10.1, Y1.3 (OUT)
SCK: R15.2; also elsewhere on the board
SCL: DS1.3 (SCL); also elsewhere on the board
SDA: DS1.4 (SDA); also elsewhere on the board
SX_RST: IC1.9 (RESET); also elsewhere on the board
~PA_EN: R2.2, U2.3 (~ON); also elsewhere on the board

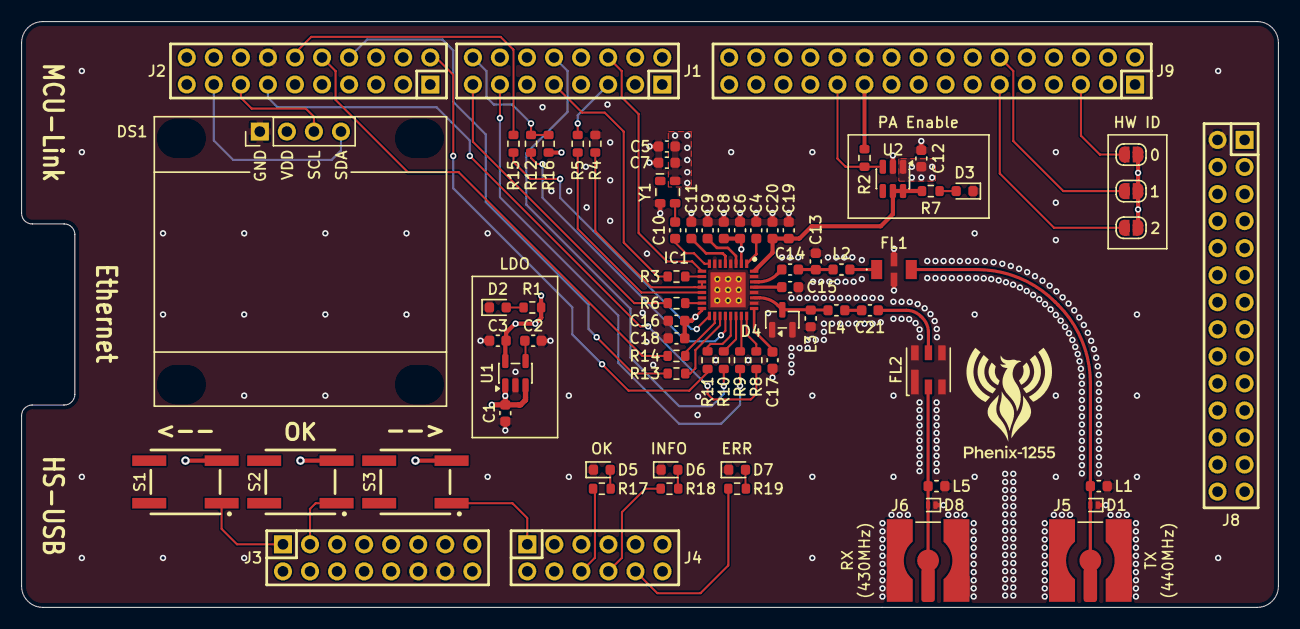
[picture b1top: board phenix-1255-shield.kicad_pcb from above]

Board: 4 copper layers, 118.0 x 55.0 mm, 74 parts (0 on the bottom side), 62 nets.

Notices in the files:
phenix-1255-shield.kicad_pcb:
Based on Phenix-1255-HW, Copyright (c) Z32IT 2026
Modifications Copyright (c) w4tchd0g (DM5LF) 2026
